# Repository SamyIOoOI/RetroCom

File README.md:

<h1 align="center">RetroCom</h1>

--------------------------
---------------------------------
## A multiple channel one-to-one (Simultaneous Speech) two-way INTERCOM built around the AT89C52-PI24 MCU // AT89S52-PU24 (8052 Core) with an Embedded FM Radio Model.

### <p align="center">[Main Features](#main-features) **-** [Variations](#variations) **-** [PCB & Schematic](#pcb--schematic-designs) **-** [Assembly Instructions](#-assembly-instructions-) **-** [Case](#case-design) **-** [BOM [Table]](#bill-of-materials) **-** [BOM [CSV]](BOM/BOM.csv) **-** [Gerber Files](/Gerber%20Files/) **-** [BOM[XLSX]](BOM/BOM%20EXCEL.xlsx)</p>

<p align="center">
&nbsp;&nbsp;&nbsp;&nbsp;&nbsp;&nbsp;&nbsp;&nbsp;
</p>

## Main Features

- AT89C52-PI24 MCU per Station. *[Handles Interstation Communication & Interface]*.
- Supports two-way simultaneous speech. No taking turns when talking. RetroCom functions just like a phonecall.
- All stations are connected to main station directly via CAT6 Cables. Distances of 20M (Meters) to 30M are **OK** .
- Switching is done by CD4051 & CD4052 ICs powered with negative & postive 5 V Rails. PreAmped Signals face no distortion.
- Audio undergoes a preamp stage under the TL072 & power amp stage under the LM386.
- The main station has a built in Radio Module. [As of Version 1.0 [WIRED] the radio is restricted to main station with prospects to expand to other stations via HF Radio models in the Wirless versions of RetroCom.]
- All the substations are powered via the Ethernet *(CAT6 if available, other 8 cable variants usable)* No power outlets are needed at the substations.
- Main station supports up to 4 stations in wired mode. Safety measures are applied in the code. No hangs happen when a station is disconnected.
- Code is written in C & compiled with SDCC. Refer to [Station1.hex](station1.hex) & [Station2.hex](station2.hex) for flash-ready code. 

**Be Aware that slight modifications to the code might be required when using different I2C Display modules. Refer to line [35 in main.c](src\main.c) .**

------------------------------------
------------------------------------
## Variations

1- 1.0.0 Wired 2-3-4-Station Package. **[Finished]**:-

- Main station + Station 2 + Station 3 + Station 4
- Code polls for all four stations.
- Main station is connected to the substations via CAT6 Wires.
- Radio control & listen-in is restricted to Station 1 [Main].
- deemed more secure due to the nature of its wired connections.

2- 1.0.0 Wireless 2-30 Station Package [Unfinished]:-
- Planned to dynamically support up to 30 or more stations
- Drops support for CAT6 Wired connections in favor of HF or UHF Radio Transmission.
- Might have security concerns related to signal interception.

-----------------------------------

## PCB & Schematic Designs

The PCB & Schematics were designed in KiCad with a focus on order & accessibility in the case of hand soldering. The RDA5807M [Main Station] is the only SMD Component.``

``All designs follow a two-layer order with the bottom layer functioning as a GND fillzone.``

**== Station 1 [Main Station] [Schematic](KiCad_PCB_Source\RetroCom.kicad_sch) ==**

**== Station 1 [Main Station] [PCB](KiCad_PCB_Source\RetroCom.kicad_pcb) ==**

``3D Model of Board - Uses DIP Sockets Instead of IC Models``

**== Station 2 [Side Station 1] [Schematic](KiCad_PCB_Source\RetroCom_Station2\RetroCom_Station2.kicad_sch) ==**

**== Station 2 [Side Station 1] [PCB](KiCad_PCB_Source\RetroCom_Station2\RetroCom_Station2.kicad_pcb) ==**

``3D Model of Board - Uses DIP Sockets Instead of IC Models``

---------------------------------
## Case Design 

The case design was made in fusion with simplicity & practicality in mind.

The design can be accessed via Fusion Share link on your browser through the [link](https://gmail6713823.autodesk360.com/g/shares/SH28cd1QT2badd0ea72b43d7afa1819b979d) provided.

21 x 13 x 5 (cm) are the dimensions of the Case.

---------------------------------
-----------------------------

## = Assembly Instructions =

1- Connecting the PCB & Case

- In the case of **hand-solder** follow the schematic's connections and use the [PCB](Graphics/PCB%20Station%201.png) Design as a reference.
- Use **DIP Sockets** for the ICs (RDA5807M is an exception as it is SMD).
- Connect the ICs & flashed AT89S52s to their respective hand-soldered/printed PCBs.
- Connect the buzzer, speaker, microphone, LEDs, toggle switches, momentary switches & I2C Display through via jumper cables from their respective headers.
- For power, connect half a female jumper wire to the screw terminals of a female DC Socket to wire terminals connector. This can be connected to a **12VDC** 3 & above Amp Wall Adapter.
- Solder the RJ45 Houses in their locations, run CAT6 Cables from each sub-station to main station. 
- For the case, if using the printed design, connect the board to its respective mounting holes via M3 Screws [8mm - 10mm]. 
- Each printed case design has eight board mounting holes to suit both board sizes (Side Stations & Main Station).
- Place the interface components on the surface panel of the case, run jumper cables to the board below. Use the four corner bound M3 screw holes for holding the panel on the bottom case piece. Run the outgoing cables through the back panel.

2- Flashing the code (.hex) files into the AT89S52 Chip.

- Place the AT89 on a breadboard & build the  crystal and reset circuits. Refer to the [Schematic](Graphics/Schematic%20Station%202.png) for details. Look for labels "**CRYS**" & "**RST**".
- Plug the USBasp into you pc/laptop USB port & select it in Zadig's drop-down menu. Install libusb-win32 or libusbK.
- Connect the ISP lines MOSI, MISO, SCK, RESET & GND. EA pin must be connected to VCC. Do not power the circuit before completion.
- Power the circuit through either: A- External 5V Supply B- USBasp's 5V Pinout.
- Use ProgISP to flash the chip. Select AT89S52 from the drop-down menu.

**[ProgISP](https://www.phippselectronics.com/support/prog-isp-software/) Software & [Zadig](https://zadig.akeo.ie/#) Drivers Installer are required to flash the chips.**

## Bill of Materials

| **Part Name**                                      | **Quantity** | **Price**    | **Link**                                                                                                                                                                                                            |
|----------------------------------------------------|--------------|----------------|---------------------------------------------------------------------------------------------------------------------------------------------------------------------------------------------------------------------|
| **33pF Capacitor**                                 | 4.00         |  EGP 2.00      | https://makerselectronics.com/product/ceramic-capacitor-33pf-50v/                                                                                                                                                   |
| **10 uF cap**                                      | 6.00         |  EGP 6.00      | https://www.ram-e-shop.com/shop/c-10u25v-capacitor-10uf-25v-6095                                                                                                                                                    |
| **220 uF Cap**                                     | 2.00         |  EGP 2.00      | https://www.ram-e-shop.com/shop/c-220u16v-capacitor-220uf-16v-5654                                                                                                                                                  |
| **4700 uF cap**                                    | 2.00         |  EGP 12.00     | https://www.ram-e-shop.com/shop/c-4700u25v-capacitor-4700uf-25v-6079                                                                                                                                                |
| **47 uF cap**                                      | 7.00         |  EGP 7.00      | https://makerselectronics.com/product/capacitor-47uf-50v/                                                                                                                                                           |
| **100 nF Cap**                                     | 18.00        |  EGP 13.50     | https://www.ram-e-shop.com/shop/c-pf-104-ceramic-capacitor-pf104-100nf-25v-6240                                                                                                                                     |
| **100 pF Cap**                                     | 1.00         |  EGP 0.50      | https://makerselectronics.com/product/ceramic-capacitor-100pf-50v/                                                                                                                                                  |
| **Yellow LED  10mm**                               | 2.00         |  EGP 6.00      | https://makerselectronics.com/product/yellow-led-transparent-10mm/                                                                                                                                                  |
| **Green LED  10mm**                                | 2.00         |  EGP 6.00      | https://makerselectronics.com/product/green-led-10mm-transparent/                                                                                                                                                   |
| **Red LED  10mm**                                  | 2.00         |  EGP 6.00      | https://makerselectronics.com/product/red-led-transparent-10mm/                                                                                                                                                     |
| **Orange LED  10mm**                               | 2.00         |  EGP 6.00      | https://makerselectronics.com/product/orange-led-10mm-transparent/                                                                                                                                                  |
| **RJ8-P-PCB (RJ45 8P8C Plastic Housing)**          | 5.00         |  EGP 25.00     | https://www.ram-e-shop.com/shop/rj8-p-pcb-rj45-8-pin-connector-on-pcb-plastic-housing-5749                                                                                                                          |
| **10K R**                                          | 14.00        |  EGP 4.00      | https://www.ram-e-shop.com/shop/carbon-resistance-1-4w-price-per-4-resistors-9506#attr=314                                                                                                                          |
| **2.2K R**                                         | 2.00         |  EGP 0.10      | https://makerselectronics.com/product/carbon-resistor-2-2k%cf%89-0-125w-through-hole/                                                                                                                               |
| **10 R**                                           | 2.00         |  EGP 1.50      | https://makerselectronics.com/product/carbon-resistor-10%cf%89-0-25w-through-hole/                                                                                                                                  |
| **470 R**                                          | 8.00         |  EGP 2.00      | https://www.ram-e-shop.com/shop/carbon-resistance-1-4w-price-per-4-resistors-9506#attr=307                                                                                                                          |
| **47k R**                                          | 1.00         |  EGP 1.50      | https://makerselectronics.com/product/carbon-resistor-47k%cf%89-0-25w/                                                                                                                                              |
| **100k R**                                         | 2.00         |  EGP 1.00      | https://www.ram-e-shop.com/shop/carbon-resistance-1-4w-price-per-4-resistors-9506#attr=317                                                                                                                          |
| **47 R**                                           | 2.00         |  EGP 0.20      | https://makerselectronics.com/product/carbon-resistor-47%cf%89-0-125w-through-hole/                                                                                                                                 |
| **220K R**                                         | 2.00         |  EGP 1.50      | https://makerselectronics.com/product/carbon-resistor-220k%cf%89-0-25w-through-hole/                                                                                                                                |
| **4.7K R**                                         | 4.00         |  EGP 1.50      | https://makerselectronics.com/product/carbon-resistor-4-7k-0-25w/                                                                                                                                                   |
| **C8050**                                          | 4.00         |  EGP 3.00      | https://www.ram-e-shop.com/shop/c8050-c8050-6050                                                                                                                                                                    |
| **11.0592MHz Crystal**                             | 2.00         |  EGP 8.00      | https://www.ram-e-shop.com/shop/o-11-0592mhz-crystal-oscillator-11-0592-mhz-5668                                                                                                                                    |
| **32.768 kHz Crystal**                             | 1.00         |  EGP 3.00      | https://www.ram-e-shop.com/shop/o-32-768khz-crystal-oscillator-32-768-khz-5880                                                                                                                                      |
| **PIN Headers x40 Male**                           | 2.00         |  EGP 6.00      | https://makerselectronics.com/product/pin-headers-male-2-54mm-40-pin-straight-black-11mm/                                                                                                                           |
| **PIN Headers x40 Female**                         | 2.00         |  EGP 10.00     | https://makerselectronics.com/product/pin-headers-female-2-54mm-40-pin/                                                                                                                                             |
| **Speakers 8 ohm 0.25 watts**                      | 2.00         |  EGP 20.00     | https://makerselectronics.com/product/speaker-8%cf%89-0-25w-o-29mm/                                                                                                                                                 |
| **Condenser Microphone**                           | 2.00         |  EGP 12.00     | https://makerselectronics.com/product/condenser-microphone-2-pins/                                                                                                                                                  |
| **I2C LCD 2x16 Modules**                           | 2.00         |  EGP 290.00    | https://www.ram-e-shop.com/shop/lcd-i2c-2x16-blue-iic-i2c-1602-serial-character-lcd-2x16-display-8884                                                                                                               |
| **4 Pin Toggle Switch DSPT**                       | 2.00         |  EGP 80.00     | https://makerselectronics.com/product/toggle-switch-4-pins-15a-e-ten1221-o/                                                                                                                                         |
| **2 Pin Toggle Switch SPST**                       | 2.00         |  EGP 40.00     | https://makerselectronics.com/product/toggle-switch-on-off-2-pin-2a-12mm/                                                                                                                                           |
| **Momentary Toggle presses/switches 8**            | 8.00         |  EGP 52.00     | https://makerselectronics.com/product/push-button-switch-on-off-2pin/                                                                                                                                               |
| **Buzzers**                                        | 2.00         |  EGP 50.00     | https://www.ram-e-shop.com/shop/buzzer12v-big-black-buzzer-big-size-3-24v-piezo-electronic-alarm-6122                                                                                                               |
| **PCB 13x25 cm2 Dotted Holes**                     | 2.00         |  EGP 97.00     | https://www.ram-e-shop.com/shop/pcb23-holes-13x25-pcb-13x25-cm2-dots-holes-sku-pcb23-6681                                                                                                                           |
| **Jumper Wire Cables Male to Male [40 Wires]**     | 2.00         |  EGP 70.00     | https://www.ram-e-shop.com/shop/ph61-mm-20cm-ph61-20cm-male-to-male-40-jumper-wires-set-7094                                                                                                                        |
| **Jumper Wire Cables Female to Female [40 Wires]** | 1.00         |  EGP 35.00     | https://www.ram-e-shop.com/shop/ph62-ff-20cm-ph62-20cm-female-to-female-40-jumper-wires-set-7189                                                                                                                    |
| **Jumper Wire Cables Male to Female [40 Wires]**   | 2.00         |  EGP 70.00     | https://www.ram-e-shop.com/shop/ph60-mf-20cm-ph60-20cm-male-to-female-40-jumper-wires-set-7066                                                                                                                      |
| **Solder Wire**                                    | 1.00         |  EGP 210.00    | https://makerselectronics.com/product/soldering-wire-100gm-alloy70-30-made/                                                                                                                                         |
| **Soldering Iron**                                 | 1.00         |  EGP 195.00    | https://www.ram-e-shop.com/shop/se860-suoer-se860-60w-basic-soldering-iron-ct-360-5600                                                                                                                              |
| **Soldering Iron Stand**                           | 1.00         |  EGP 45.00     | https://makerselectronics.com/product/no-218-soldering-iron-stand/                                                                                                                                                  |
| **Soldering Paste**                                | 1.00         |  EGP 25.00     | https://makerselectronics.com/product/yx-18-flux-soldering-paste/?attribute_size=50g                                                                                                                                |
| **Fares USBasp AVR programmer**                    | 1.00         |  EGP 175.00    | https://www.ram-e-shop.com/shop/prog-avr-fares-fares-usbasp-avr-programmer-8325                                                                                                                                     |
| **20 Meter CAT6 Cable**                            | 1.00         |  EGP 165.00    | https://makerselectronics.com/product/zlink-cable-cat6-ethernet-patch-cord/                                                                                                                                         |
| **12 VDC Wall Power Adapter**                      | 1.00         |  EGP 135.00    | https://www.ram-e-shop.com/shop/adapter-fixed-12v-3a-wall-power-adapter-12vdc-3a-high-quality-adapter-5573                                                                                                          |
| **Female DC Jack Adapter with Terminal Block**     | 1.00         |  EGP 7.00      | https://makerselectronics.com/product/female-dc-jack-adapter-terminals/                                                                                                                                             |
| **AT89S52-PU24**                                   | 2.00         |  EGP 170.00    | https://makerselectronics.com/product/at89s52-24pu-8kb-4v5-5v-256byte-24/                                                                                                                                           |
| **IC Socket DIP-40**                               | 2.00         |  EGP 10.00     | https://www.ram-e-shop.com/shop/n20-20-ic-socket-n20-20-base-40-pin-5902                                                                                                                                            |
| **IC Socket DIP-16**                               | 3.00         |  EGP 5.25      | https://makerselectronics.com/product/ic-socket-88-base-16-pin/                                                                                                                                                     |
| **CD4051**                                         | 2.00         |  EGP 30.00     | https://www.ram-e-shop.com/shop/4051-ic-4051-single-8-channel-multiplexer-demultiplexer-5551                                                                                                                        |
| **CD4052BE**                                       | 1.00         |  EGP 9.00      | https://makerselectronics.com/product/cd4052be-dual-4-channel-analog/                                                                                                                                               |
| **IC Socket DIP-8**                                | 10.00        |  EGP 7.50      | https://www.ram-e-shop.com/shop/n4-4-ic-socket-n4-4-base-8-pin-5864                                                                                                                                                 |
| **TL072CN**                                        | 2.00         |  EGP 34.00     | https://www.ram-e-shop.com/shop/tl072-tl072cn-5722                                                                                                                                                                  |
| **LM386N**                                         | 2.00         |  EGP 12.00     | https://www.ram-e-shop.com/shop/lm386-lm386n-5927                                                                                                                                                                   |
| **ICL7660**                                        | 2.00         |  EGP 102.60    | https://uge-one.com/product/icl7660/                                                                                                                                                                                |
| **MAX485CPA+**                                     | 4.00         |  EGP 72.00     | https://makerselectronics.com/product/ic-max485cpa-low-power-transceiver-dip-8/                                                                                                                                     |
| **LM7805 Regulator**                               | 2.00         |  EGP 10.00     | https://makerselectronics.com/product/lm7805-voltage-regulator-to-220-5v/                                                                                                                                           |
| **LD33CV Regulator**                               | 1.00         |  EGP 20.00     | https://www.ram-e-shop.com/shop/ld1117v33-ld1117v33-ld33cv-6735                                                                                                                                                     |
| **TO-220 Regulator Heat Sink**                     | 3.00         |  EGP 10.50     | https://www.ram-e-shop.com/shop/hs2-aluminum-heatsink-hs-2-size-25x14x10-mm-5981                                                                                                                                    |
| **Logic level Converter Module**                   | 1.00         |  EGP 28.50     | https://uge-one.com/product/bi-directional-4-way-level-conversion-module/?gad_source=1&gad_campaignid=24034682861&gclid=CjwKCAjw4dDTBhAqEiwAkHYmSi15wnBhh5vjV9PTNDUeKMSZ1iojFyjaDYYeGKExxMUaX75Kg8KlMhoCpS4QAvD_BwE |
| **Metal Potentiometer 10K? 3-Pin**                 | 2.00         |  EGP 11.00     | https://makerselectronics.com/product/metal-potentiometer-10k%cf%89-3-pin/                                                                                                                                          |
| **RDA5807M**                                       | 1.00         |  EGP 55.00     | https://uge-one.com/product/rda5807m-fm-radio-receiver-smd-ic-msop1                                                                                                                                                 |
| ****                                               |              |  EGP 2,495.65  |                                                                                                                                                                                                                     |
| ****                                               |              |                |                                                                                                                                                                                                                     |
| **Note: Most resistors come in pack of 10s - 4s**  |              |                |                                                                                                                                                                                                                     |
| ****                                               |              |                |                                                                                                                                                                                                                     |
| **Shipping: RAM**                                  |              |  EGP 105.00    |                                                                                                                                                                                                                     |
| **Shipping: Makers Electronics**                   | 80 - 75      |  EGP 80.00     |                                                                                                                                                                                                                     |
| **Shipping: UGE Electronics**                      |              |  EGP 188.10    |                                                                                                                                                                                                                     |
| **VAT: UGE Electronics**                           |              |  EGP 45.95     |                                                                                                                                                                                                                     |
| ****                                               |              |  EGP 419.05    |                                                                                                                                                                                                                     |
| ****                                               |              |                |                                                                                                                                                                                                                     |
| ****                                               |              |  EGP 2,914.70  |                                                                                                                                                                                                                     |

## Credits

[Kicad](https://www.kicad.org/) : Schematic & PCB designs

[Autodesk Fusion](https://www.autodesk.com/ae/products/fusion-360/overview) : 3D Case Design

[Visual Studio Code](https://code.visualstudio.com/) : Logic Code Design

[Embedded IDE For VSCode](https://em-ide.com/en/) : Compiling C files into .hex format

[Notaroomba Cyberboard](https://github.com/notaroomba/cyberboard#key-features) : Inspired readme format

[tableconvert.com](https://tableconvert.com/excel-to-markdown) : Turned my xlsx table to markdown format

## Licence

Made by SamyIOoOI on github under the GPL-3.0 Licence.

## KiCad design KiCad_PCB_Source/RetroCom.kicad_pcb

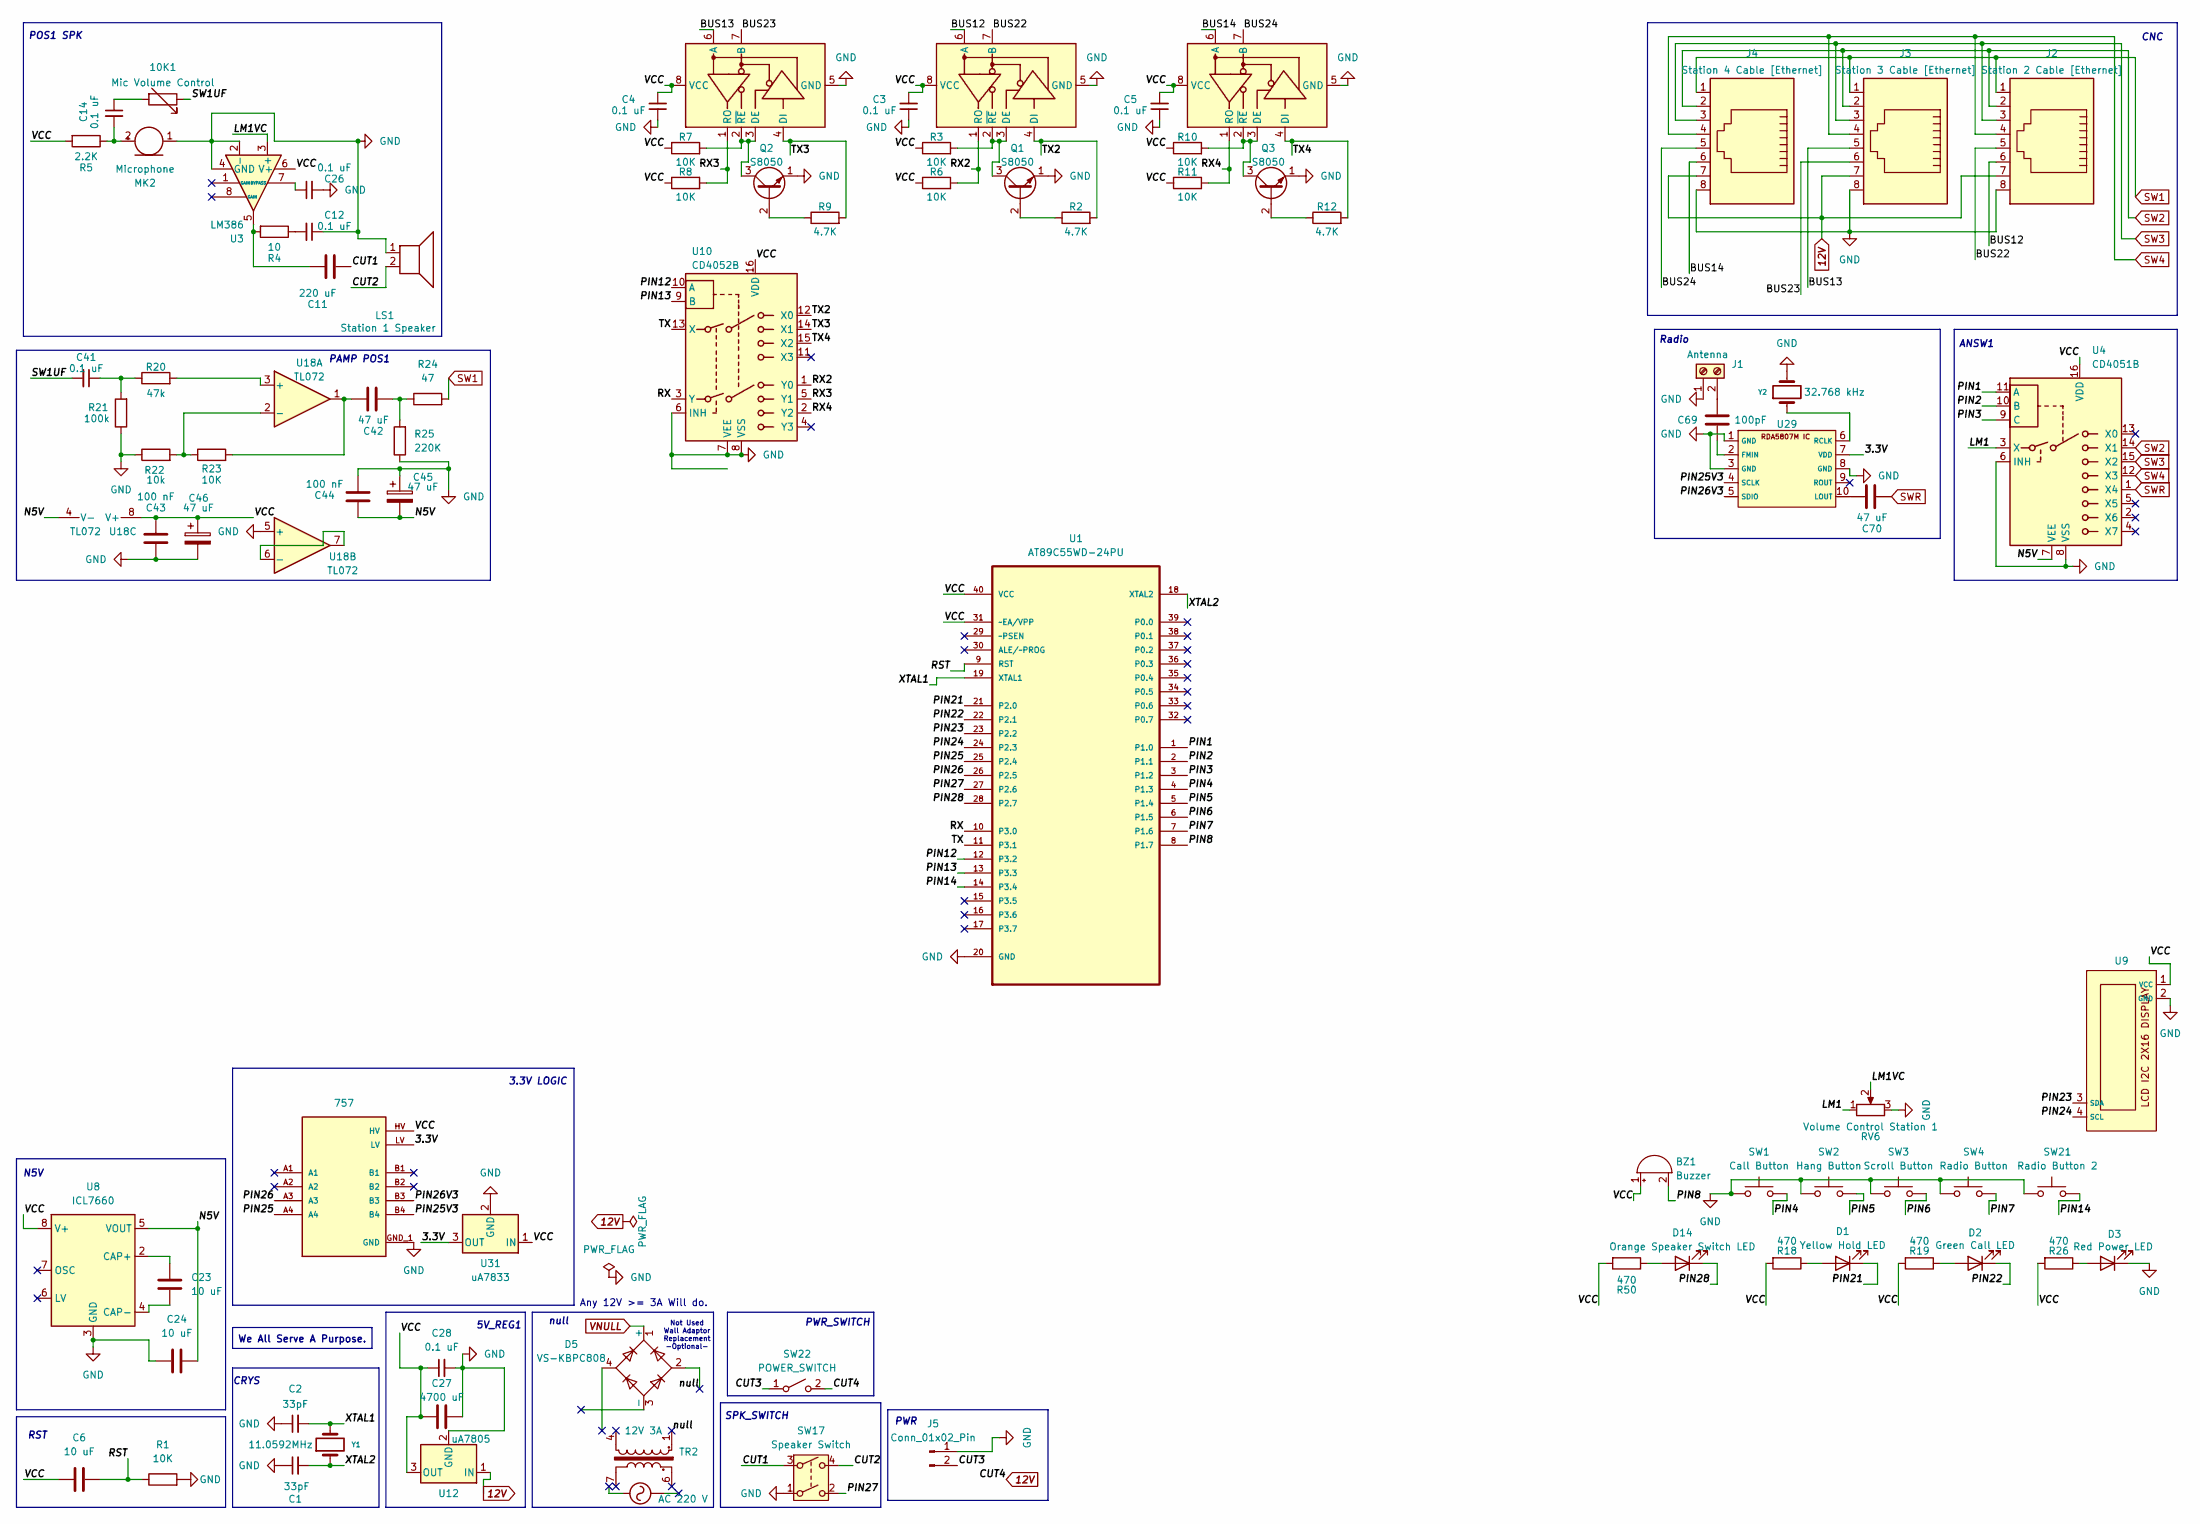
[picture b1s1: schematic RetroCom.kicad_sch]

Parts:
10K1: Mic Volume Control; PinHeader_1x02_P1.00mm_Horizontal
BZ1: Buzzer; PinHeader_1x02_P1.00mm_Horizontal
C1, C2: 33pF; C_Disc_D5.0mm_W2.5mm_P5.00mm
C3, C4, C5, C12, C14, C26, C28, C41: 0.1 uF; C_Disc_D3.8mm_W2.6mm_P2.50mm
C6, C23, C24: 10 uF; CP_Radial_D5.0mm_P2.50mm
C11: 220 uF; CP_Radial_D6.3mm_P2.50mm
C27: 4700 uF; CP_Radial_D16.0mm_P7.50mm
C42, C45, C46, C70: 47 uF; CP_Radial_D6.3mm_P2.50mm
C43, C44: 100 nF; C_Disc_D3.8mm_W2.6mm_P2.50mm
C69: 100pF; C_Disc_D3.8mm_W2.6mm_P2.50mm
D1: Yellow Hold LED; PinHeader_1x02_P2.54mm_Vertical
D2: Green Call LED; PinHeader_1x02_P2.54mm_Vertical
D3: Red Power LED; PinHeader_1x02_P2.54mm_Vertical
D5: VS-KBPC808; Diode_Bridge_Vishay_KBPC6
D14: Orange Speaker Switch LED; PinHeader_1x02_P2.54mm_Vertical
J1: Antenna; TerminalBlock_Phoenix_MKDS-1,5-2_1x02_P5.00mm_Horizontal
J2: Station 2 Cable [Ethernet]; RJ45_Amphenol_RJHSE5380
J3: Station 3 Cable [Ethernet]; RJ45_Amphenol_RJHSE5380
J4: Station 4 Cable [Ethernet]; RJ45_Amphenol_RJHSE5380
J5: Conn_01x02_Pin; PinHeader_1x02_P2.54mm_Vertical
LS1: Station 1 Speaker; PinHeader_1x02_P2.54mm_Vertical
MK2: Microphone; PinHeader_1x02_P2.54mm_Vertical
Q1, Q2, Q3: S8050; TO-92_Inline
R1, R3, R6, R7, R8, R10, R11, R23: 10K; R_Axial_DIN0207_L6.3mm_D2.5mm_P7.62mm_Horizontal
R2, R9, R12: 4.7K; R_Axial_DIN0207_L6.3mm_D2.5mm_P7.62mm_Horizontal
R4: 10; R_Axial_DIN0207_L6.3mm_D2.5mm_P7.62mm_Horizontal
R5: 2.2K; R_Axial_DIN0207_L6.3mm_D2.5mm_P7.62mm_Horizontal
R18, R19, R26, R50: 470; R_Axial_DIN0207_L6.3mm_D2.5mm_P7.62mm_Horizontal
R20: 47k; R_Axial_DIN0207_L6.3mm_D2.5mm_P7.62mm_Horizontal
R21: 100k; R_Axial_DIN0207_L6.3mm_D2.5mm_P7.62mm_Horizontal
R22: 10k; R_Axial_DIN0207_L6.3mm_D2.5mm_P7.62mm_Horizontal
R24: 47; R_Axial_DIN0207_L6.3mm_D2.5mm_P7.62mm_Horizontal
R25: 220K; R_Axial_DIN0207_L6.3mm_D2.5mm_P7.62mm_Horizontal
RV6: Volume Control Station 1; PinHeader_1x03_P2.54mm_Vertical
SW1: Call Button; PinHeader_1x02_P2.54mm_Vertical
SW2: Hang Button; PinHeader_1x02_P2.54mm_Vertical
SW3: Scroll Button; PinHeader_1x02_P2.54mm_Vertical
SW4: Radio Button; PinHeader_1x02_P2.54mm_Vertical
SW17: Speaker Switch; PinHeader_1x04_P2.54mm_Vertical
SW21: Radio Button 2; PinHeader_1x02_P2.54mm_Vertical
SW22: POWER_SWITCH; PinHeader_1x02_P2.54mm_Vertical
TR2: 12V 3A; FanPinHeader_1x04_P2.54mm_Vertical
U1: AT89C55WD-24PU; DIP-40_W15.24mm_Socket; MPN AT89C55WD-24PU
U2: 757; MODULE_757; PARTREV N/A
U3: LM386; DIP-8_W7.62mm_Socket
U4: CD4051B; DIP-16_W7.62mm_Socket
U5, U6, U11: MAX485E; DIP-8_W7.62mm_Socket
U8: ICL7660; DIP-8_W7.62mm_Socket
U9: PinHeader_1x04_P2.54mm_Vertical
U10: CD4052B; DIP-16_W7.62mm_Socket
U12: uA7805; TO-220-3_Horizontal_TabUp
U18: TL072; DIP-8_W7.62mm_Socket
U29: MSOP-10_3x3mm_P0.5mm
U31: uA7833; TO-220-3_Horizontal_TabUp
Y1: 11.0592MHz; Crystal_HC49-U_Vertical
Y2: 32.768 kHz; Crystal_C26-LF_D2.1mm_L6.5mm_Horizontal

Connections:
12V: J2.7, J3.7, J4.7, SW22.2 (B), U12.1 (IN)
/3.3V: U2.LV, U29.7 (VDD), U31.3 (OUT)
/BUS12: J2.6, U11.6 (A)
/BUS13: J3.5, U5.6 (A)
/BUS14: J4.6, U6.6 (A)
/BUS22: J2.5, U11.7 (B)
/BUS23: J3.6, U5.7 (B)
/BUS24: J4.5, U6.7 (B)
/CUT1: C11.2, SW17.3
/CUT2: LS1.2, SW17.4
/CUT3: J5.2, SW22.1 (A)
/LM1: RV6.1, U4.3 (X)
/LM1VC: RV6.2, U3.3 (+)
/N5V: C24.1, C44.2, C45.2, U4.7 (VEE), U8.5 (VOUT), U18.4 (V-)
/PIN1: U1.1 (P1.0), U4.11 (A)
/PIN2: U1.2 (P1.1), U4.10 (B)
/PIN3: U1.3 (P1.2), U4.9 (C)
/PIN4: SW1.2, U1.4 (P1.3)
/PIN5: SW2.2, U1.5 (P1.4)
/PIN6: SW3.2, U1.6 (P1.5)
/PIN7: SW4.2, U1.7 (P1.6)
/PIN8: BZ1.2 (-), U1.8 (P1.7)
/PIN12: U1.12 (P3.2), U10.10 (A)
/PIN13: U1.13 (P3.3), U10.9 (B)
/PIN14: SW21.2, U1.14 (P3.4)
/PIN21: D1.1 (K), U1.21 (P2.0)
/PIN22: D2.1 (K), U1.22 (P2.1)
/PIN23: U1.23 (P2.2), U9.3 (SDA)
/PIN24: U1.24 (P2.3), U9.4 (SCL)
/PIN25: U1.25 (P2.4), U2.A4
/PIN25V3: U2.B4, U29.4 (SCLK)
/PIN26: U1.26 (P2.5), U2.A3
/PIN26V3: U2.B3, U29.5 (SDIO)
/PIN27: SW17.2, U1.27 (P2.6)
/PIN28: D14.1 (K), U1.28 (P2.7)
/RST: C6.1, R1.1, U1.9 (RST)
/RX: U1.10 (P3.0), U10.3 (Y)
/RX2: R6.2, U10.1 (Y0), U11.1 (RO)
/RX3: R8.2, U5.1 (RO), U10.5 (Y1)
/RX4: R11.2, U6.1 (RO), U10.2 (Y2)
/SW1UF: 10K1.1, C41.2
/TX: U1.11 (P3.1), U10.13 (X)
/TX2: R2.2, U10.12 (X0), U11.4 (DI)
/TX3: R9.2, U5.4 (DI), U10.14 (X1)
/TX4: R12.2, U6.4 (DI), U10.15 (X2)
/VCC: BZ1.1 (+), C3.2, C4.2, C5.2, C6.2, C27.1, C28.1, C43.1, C46.1, R3.1, R5.2, R6.1, R7.1, R8.1, R10.1, R11.1, R18.2, R19.2, R26.2, R50.2, U1.31 (~EA/VPP), U1.40 (VCC), U2.HV, U3.6 (V+), U4.16 (VDD), U5.8 (VCC), U6.8 (VCC), U8.8 (V+), U9.1 (VCC), U10.16 (VDD), U11.8 (VCC), U12.3 (OUT), U18.8 (V+), U31.1 (IN)
/XTAL1: C2.2, U1.19 (XTAL1), Y1.2
/XTAL2: C1.2, U1.18 (XTAL2), Y1.1
GND: C1.1, C2.1, C3.1, C4.1, C5.1, C12.1, C24.2, C26.2, C27.2, C28.2, C43.2, C44.1, C45.1, C46.2, D3.1 (K), J1.1, J2.8, J3.8, J4.8, J5.1, LS1.1, MK2.1 (-), Q1.1 (E), Q2.1 (E), Q3.1 (E), R1.2, R21.1, R22.1, R25.1, RV6.3, SW1.1, SW2.1, SW3.1, SW4.1, SW17.1, SW21.1, U1.20 (GND), U2.GND_1 (GND), U2.GND_2 (GND), U3.2 (-), U3.4 (GND), U4.6 (INH), U4.8 (VSS), U5.5 (GND), U6.5 (GND), U8.3 (GND), U9.2 (GND), U10.6 (INH), U10.7 (VEE), U10.8 (VSS), U11.5 (GND), U12.2 (GND), U18.5 (+), U29.1 (GND), U29.3 (GND), U29.8 (GND), U31.2 (GND), Y2.2
unnamed: 10K1.2, C14.1
unnamed: C11.1, R4.2, U3.5
unnamed: C12.2, R4.1
unnamed: C41.1, R20.1, R21.2
unnamed: C42.1, R23.2, U18.1
unnamed: C42.2, R24.1, R25.2
unnamed: D1.2 (A), R18.1
unnamed: D2.2 (A), R19.1
unnamed: D3.2 (A), R26.1
unnamed: D5.2, TR2.1
unnamed: D14.2 (A), R50.1
unnamed: C69.1, J1.2
unnamed: C14.2, MK2.2 (+), R5.1
unnamed: Q1.2 (B), R2.1
unnamed: Q1.3 (C), R3.2, U11.2 (~RE), U11.3 (DE)
unnamed: Q2.2 (B), R9.1
unnamed: Q2.3 (C), R7.2, U5.2 (~RE), U5.3 (DE)
unnamed: Q3.2 (B), R12.1
unnamed: Q3.3 (C), R10.2, U6.2 (~RE), U6.3 (DE)
unnamed: C26.1, U3.7 (BYPASS)
unnamed: C23.1, U8.2 (CAP+)
unnamed: C23.2, U8.4 (CAP-)
unnamed: R20.2, U18.3 (+)
unnamed: R22.2, R23.1, U18.2 (-)
unnamed: U18.6 (-), U18.7
unnamed: C69.2, U29.2 (FMIN)
unnamed: C70.1, U29.10 (LOUT)
unnamed: U29.6 (RCLK), Y2.1
SW1: J2.1, J3.1, J4.1, R24.2
SW2: J2.2, J3.2, J4.2, U4.14 (X1)
SW3: J2.3, J3.3, J4.3, U4.15 (X2)
SW4: J2.4, J3.4, J4.4, U4.12 (X3)
SWR: C70.2, U4.1 (X4)

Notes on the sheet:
3.3V LOGIC
We All Serve A Purpose.
Radio
CNC
POS1 SPK
5V_REG1
PWR
PWR_SWITCH
RST
Not Used Wall Adaptor Replacement -Optional-
ANSW1
SPK_SWITCH
N5V
CRYS
PAMP POS1
null
Any 12V >= 3A Will do.

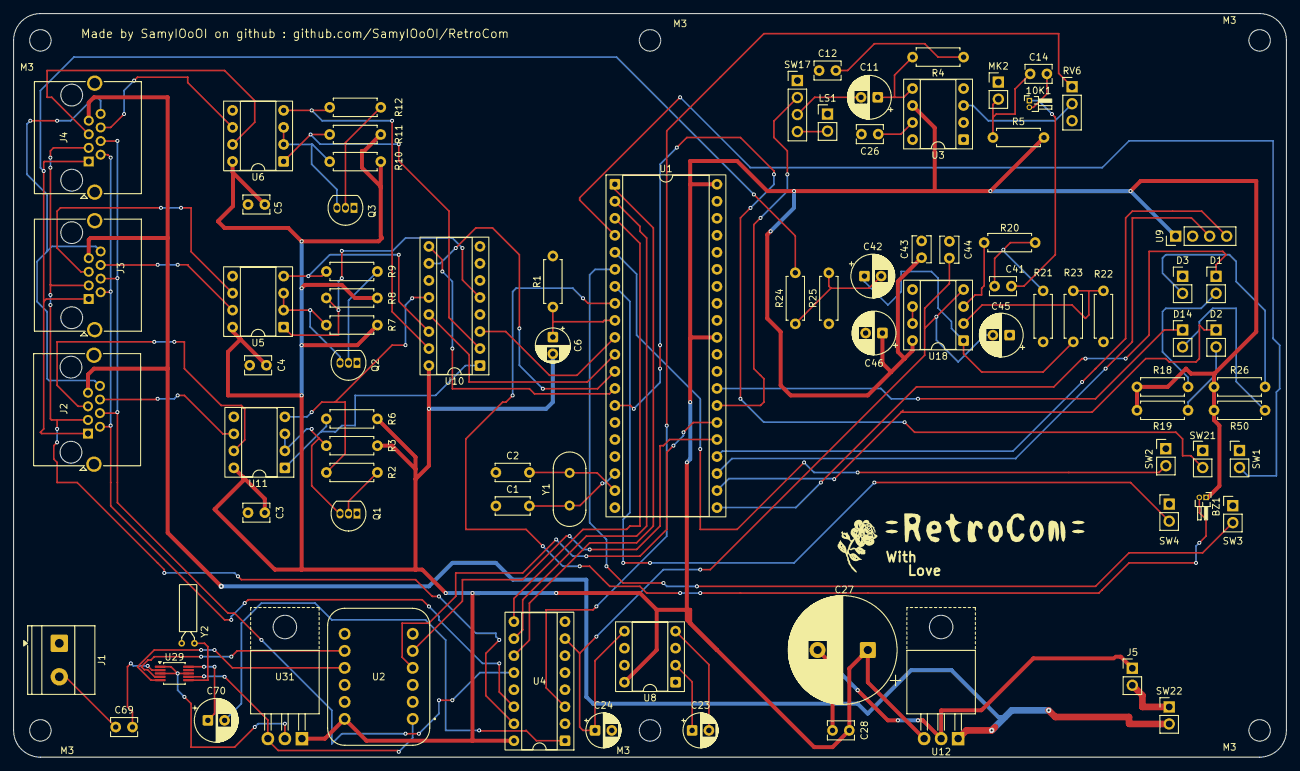
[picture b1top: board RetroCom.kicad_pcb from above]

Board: 2 copper layers, 190.0 x 111.0 mm, 90 parts (0 on the bottom side), 81 nets.

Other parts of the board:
M3, M3#2, M3#3, M3#4, M3#5, M3#6: MountingHole_3.2mm_M3

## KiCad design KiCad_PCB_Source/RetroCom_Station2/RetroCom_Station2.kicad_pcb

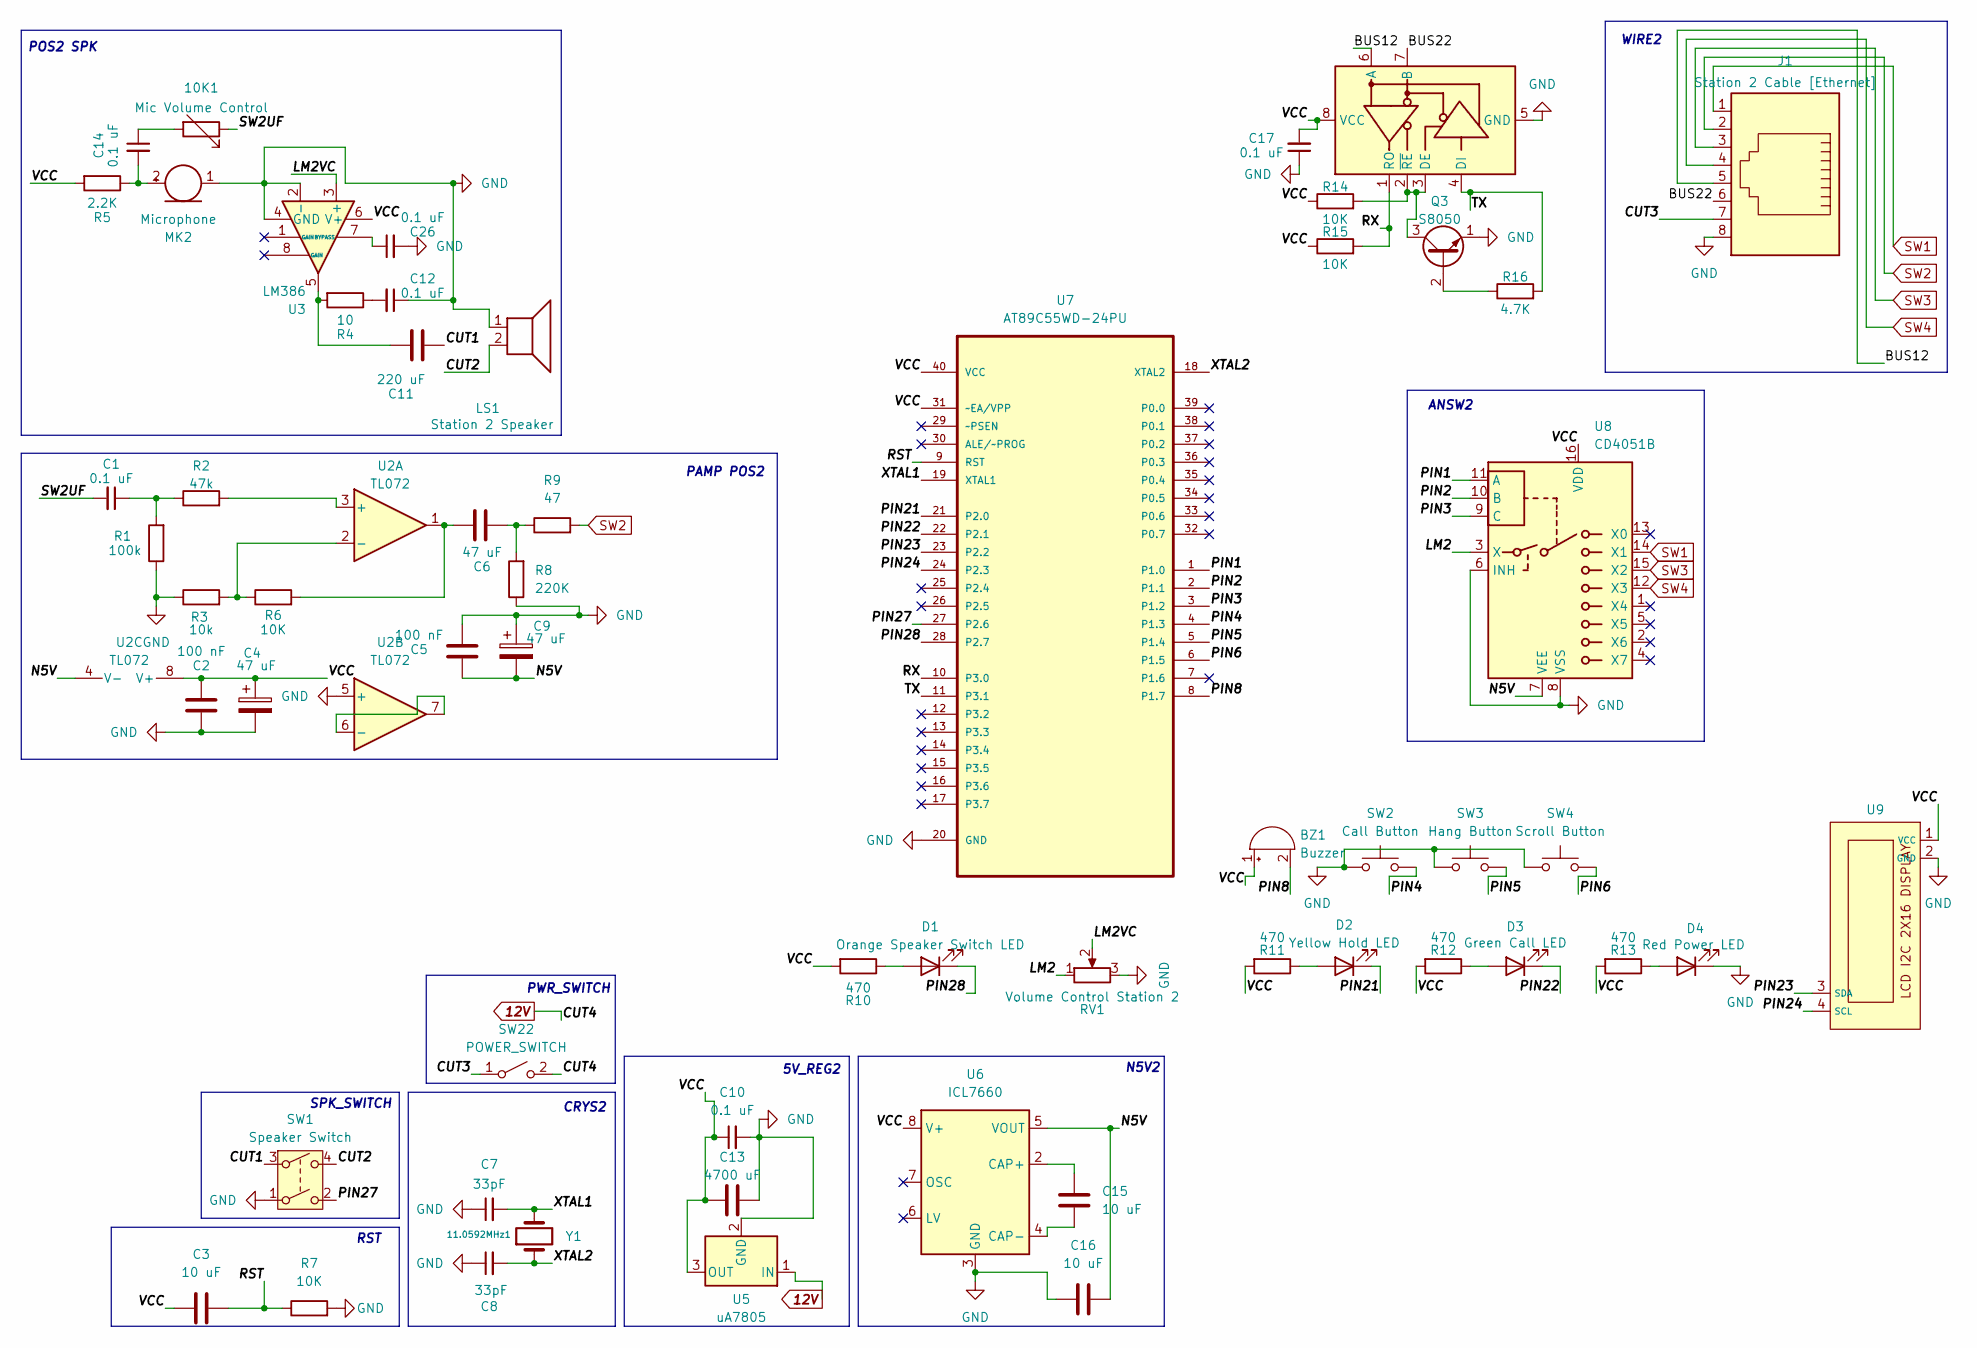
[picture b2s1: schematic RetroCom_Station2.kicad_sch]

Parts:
10K1: Mic Volume Control; PinHeader_1x02_P1.00mm_Horizontal
11.0592MHz1: Y1; Crystal_HC49-U_Vertical
BZ1: Buzzer; PinHeader_1x02_P1.00mm_Horizontal
C1, C10, C12, C14, C17, C26: 0.1 uF; C_Disc_D3.8mm_W2.6mm_P2.50mm
C2, C5: 100 nF; C_Disc_D3.8mm_W2.6mm_P2.50mm
C3, C15, C16: 10 uF; CP_Radial_D5.0mm_P2.50mm
C4, C6, C9: 47 uF; CP_Radial_D6.3mm_P2.50mm
C7, C8: 33pF; C_Disc_D5.0mm_W2.5mm_P5.00mm
C11: 220 uF; CP_Radial_D6.3mm_P2.50mm
C13: 4700 uF; CP_Radial_D16.0mm_P7.50mm
D1: Orange Speaker Switch LED; PinHeader_1x02_P2.54mm_Vertical
D2: Yellow Hold LED; PinHeader_1x02_P2.54mm_Vertical
D3: Green Call LED; PinHeader_1x02_P2.54mm_Vertical
D4: Red Power LED; PinHeader_1x02_P2.54mm_Vertical
J1: Station 2 Cable [Ethernet]; RJ45_Amphenol_RJHSE5380
LS1: Station 2 Speaker; PinHeader_1x02_P2.54mm_Vertical
MK2: Microphone; PinHeader_1x02_P2.54mm_Vertical
Q3: S8050; TO-92_Inline
R1: 100k; R_Axial_DIN0207_L6.3mm_D2.5mm_P7.62mm_Horizontal
R2: 47k; R_Axial_DIN0207_L6.3mm_D2.5mm_P7.62mm_Horizontal
R3: 10k; R_Axial_DIN0207_L6.3mm_D2.5mm_P7.62mm_Horizontal
R4: 10; R_Axial_DIN0207_L6.3mm_D2.5mm_P7.62mm_Horizontal
R5: 2.2K; R_Axial_DIN0207_L6.3mm_D2.5mm_P7.62mm_Horizontal
R6, R7, R14, R15: 10K; R_Axial_DIN0207_L6.3mm_D2.5mm_P7.62mm_Horizontal
R8: 220K; R_Axial_DIN0207_L6.3mm_D2.5mm_P7.62mm_Horizontal
R9: 47; R_Axial_DIN0207_L6.3mm_D2.5mm_P7.62mm_Horizontal
R10, R11, R12, R13: 470; R_Axial_DIN0207_L6.3mm_D2.5mm_P7.62mm_Horizontal
R16: 4.7K; R_Axial_DIN0207_L6.3mm_D2.5mm_P7.62mm_Horizontal
RV1: Volume Control Station 2; PinHeader_1x03_P2.54mm_Vertical
SW1: Speaker Switch; PinHeader_1x04_P2.54mm_Vertical
SW2: Call Button; PinHeader_1x02_P2.54mm_Vertical
SW3: Hang Button; PinHeader_1x02_P2.54mm_Vertical
SW4: Scroll Button; PinHeader_1x02_P2.54mm_Vertical
SW22: POWER_SWITCH; PinHeader_1x02_P2.54mm_Vertical
U1: MAX485E; DIP-8_W7.62mm_Socket
U2: TL072; DIP-8_W7.62mm_Socket
U3: LM386; DIP-8_W7.62mm_Socket
U5: uA7805; TO-220-3_Horizontal_TabUp
U6: ICL7660; DIP-8_W7.62mm_Socket
U7: AT89C55WD-24PU; DIP-40_W15.24mm_Socket; MPN AT89C55WD-24PU
U8: CD4051B; DIP-16_W7.62mm_Socket
U9: PinHeader_1x04_P2.54mm_Vertical

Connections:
12V: SW22.2 (B), U5.1 (IN)
/BUS12: J1.5, U1.6 (A)
/BUS22: J1.6, U1.7 (B)
/CUT1: C11.2, SW1.3
/CUT2: LS1.2, SW1.4
/CUT3: J1.7, SW22.1 (A)
/LM2: RV1.1, U8.3 (X)
/LM2VC: RV1.2, U3.3 (+)
/N5V: C5.2, C9.2, C16.1, U2.4 (V-), U6.5 (VOUT), U8.7 (VEE)
/PIN1: U7.1 (P1.0), U8.11 (A)
/PIN2: U7.2 (P1.1), U8.10 (B)
/PIN3: U7.3 (P1.2), U8.9 (C)
/PIN4: SW2.2, U7.4 (P1.3)
/PIN5: SW3.2, U7.5 (P1.4)
/PIN6: SW4.2, U7.6 (P1.5)
/PIN8: BZ1.2 (-), U7.8 (P1.7)
/PIN21: D2.1 (K), U7.21 (P2.0)
/PIN22: D3.1 (K), U7.22 (P2.1)
/PIN23: U7.23 (P2.2), U9.3 (SDA)
/PIN24: U7.24 (P2.3), U9.4 (SCL)
/PIN27: SW1.2, U7.27 (P2.6)
/PIN28: D1.1 (K), U7.28 (P2.7)
/RST: C3.1, R7.1, U7.9 (RST)
/RX: R15.2, U1.1 (RO), U7.10 (P3.0)
/SW2UF: 10K1.1, C1.2
/TX: R16.2, U1.4 (DI), U7.11 (P3.1)
/VCC: BZ1.1 (+), C2.1, C3.2, C4.1, C10.1, C13.1, C17.2, R5.2, R10.2, R11.2, R12.2, R13.2, R14.1, R15.1, U1.8 (VCC), U2.8 (V+), U3.6 (V+), U5.3 (OUT), U6.8 (V+), U7.31 (~EA/VPP), U7.40 (VCC), U8.16 (VDD), U9.1 (VCC)
/XTAL1: 11.0592MHz1.2, C7.2, U7.19 (XTAL1)
/XTAL2: 11.0592MHz1.1, C8.2, U7.18 (XTAL2)
GND: C2.2, C4.2, C5.1, C7.1, C8.1, C9.1, C10.2, C12.1, C13.2, C16.2, C17.1, C26.2, D4.1 (K), J1.8, LS1.1, MK2.1 (-), Q3.1 (E), R1.1, R3.1, R7.2, R8.1, RV1.3, SW1.1, SW2.1, SW3.1, SW4.1, U1.5 (GND), U2.5 (+), U3.2 (-), U3.4 (GND), U5.2 (GND), U6.3 (GND), U7.20 (GND), U8.6 (INH), U8.8 (VSS), U9.2 (GND)
unnamed: 10K1.2, C14.1
unnamed: C1.1, R1.2, R2.1
unnamed: C6.1, R6.2, U2.1
unnamed: C6.2, R8.2, R9.1
unnamed: C11.1, R4.2, U3.5
unnamed: C12.2, R4.1
unnamed: D1.2 (A), R10.1
unnamed: D2.2 (A), R11.1
unnamed: D3.2 (A), R12.1
unnamed: D4.2 (A), R13.1
unnamed: C14.2, MK2.2 (+), R5.1
unnamed: Q3.2 (B), R16.1
unnamed: Q3.3 (C), R14.2, U1.2 (~RE), U1.3 (DE)
unnamed: R2.2, U2.3 (+)
unnamed: R3.2, R6.1, U2.2 (-)
unnamed: U2.6 (-), U2.7
unnamed: C26.1, U3.7 (BYPASS)
unnamed: C15.1, U6.2 (CAP+)
unnamed: C15.2, U6.4 (CAP-)
SW1: J1.1, U8.14 (X1)
SW2: J1.2, R9.2
SW3: J1.3, U8.15 (X2)
SW4: J1.4, U8.12 (X3)

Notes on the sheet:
PAMP POS2
PWR_SWITCH
CRYS2
POS2 SPK
5V_REG2
SPK_SWITCH
WIRE2
ANSW2
N5V2
RST

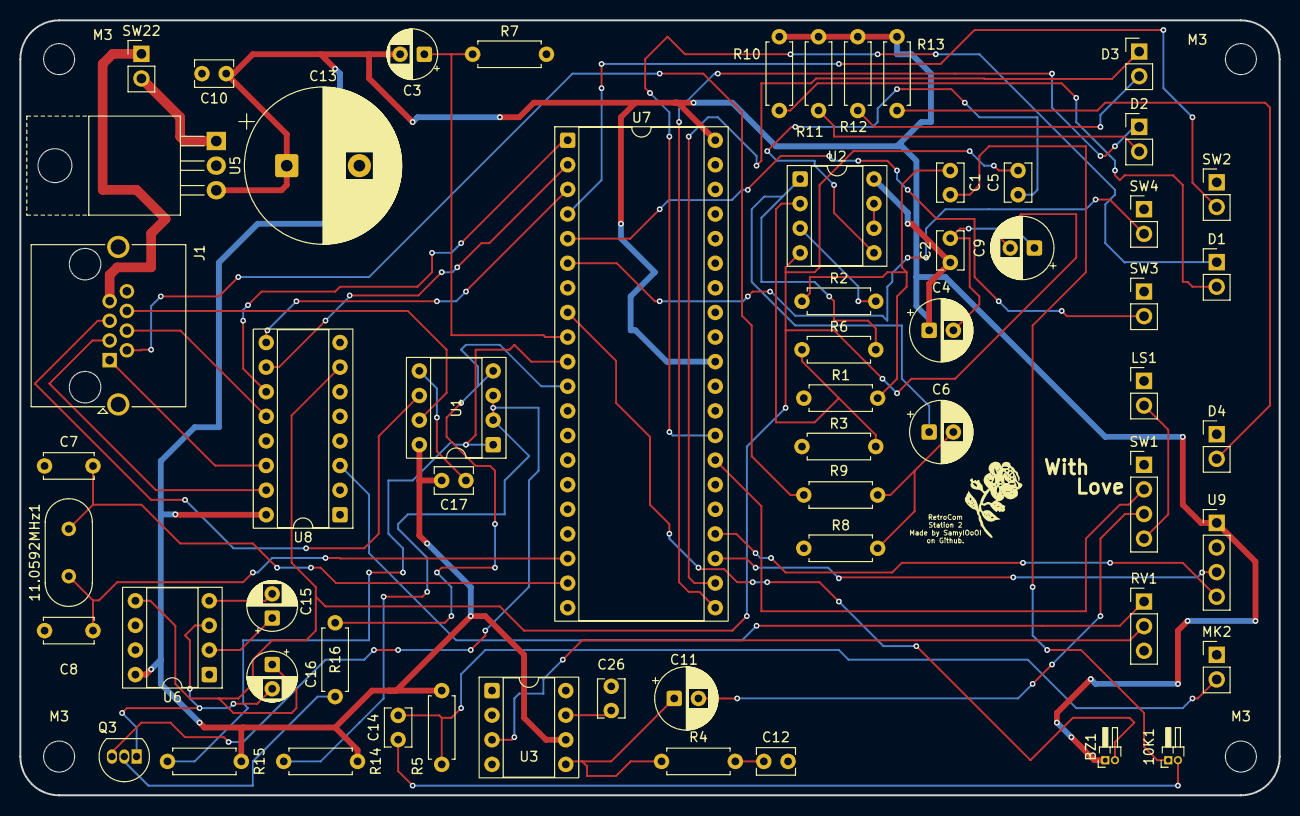
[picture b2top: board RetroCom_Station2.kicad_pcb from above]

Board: 2 copper layers, 130.0 x 80.0 mm, 63 parts (0 on the bottom side), 53 nets.

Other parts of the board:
M3, M3#2, M3#3, M3#4: MountingHole_3.2mm_M3

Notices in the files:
README.md:
Licence:
Made by SamyIOoOI on github under the GPL-3.0 Licence.
